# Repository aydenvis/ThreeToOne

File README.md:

# threetoone

*A short description of the keyboard/project*

* Keyboard Maintainer: [Ayden Visser](https://github.com/yourusername)
* Hardware Supported: *The PCBs, controllers supported*
* Hardware Availability: *Links to where you can find this hardware*

Make example for this keyboard (after setting up your build environment):

    make threetoone:default

Flashing example for this keyboard:

    make threetoone:default:flash

See the [build environment setup](https://docs.qmk.fm/#/getting_started_build_tools) and the [make instructions](https://docs.qmk.fm/#/getting_started_make_guide) for more information. Brand new to QMK? Start with our [Complete Newbs Guide](https://docs.qmk.fm/#/newbs).

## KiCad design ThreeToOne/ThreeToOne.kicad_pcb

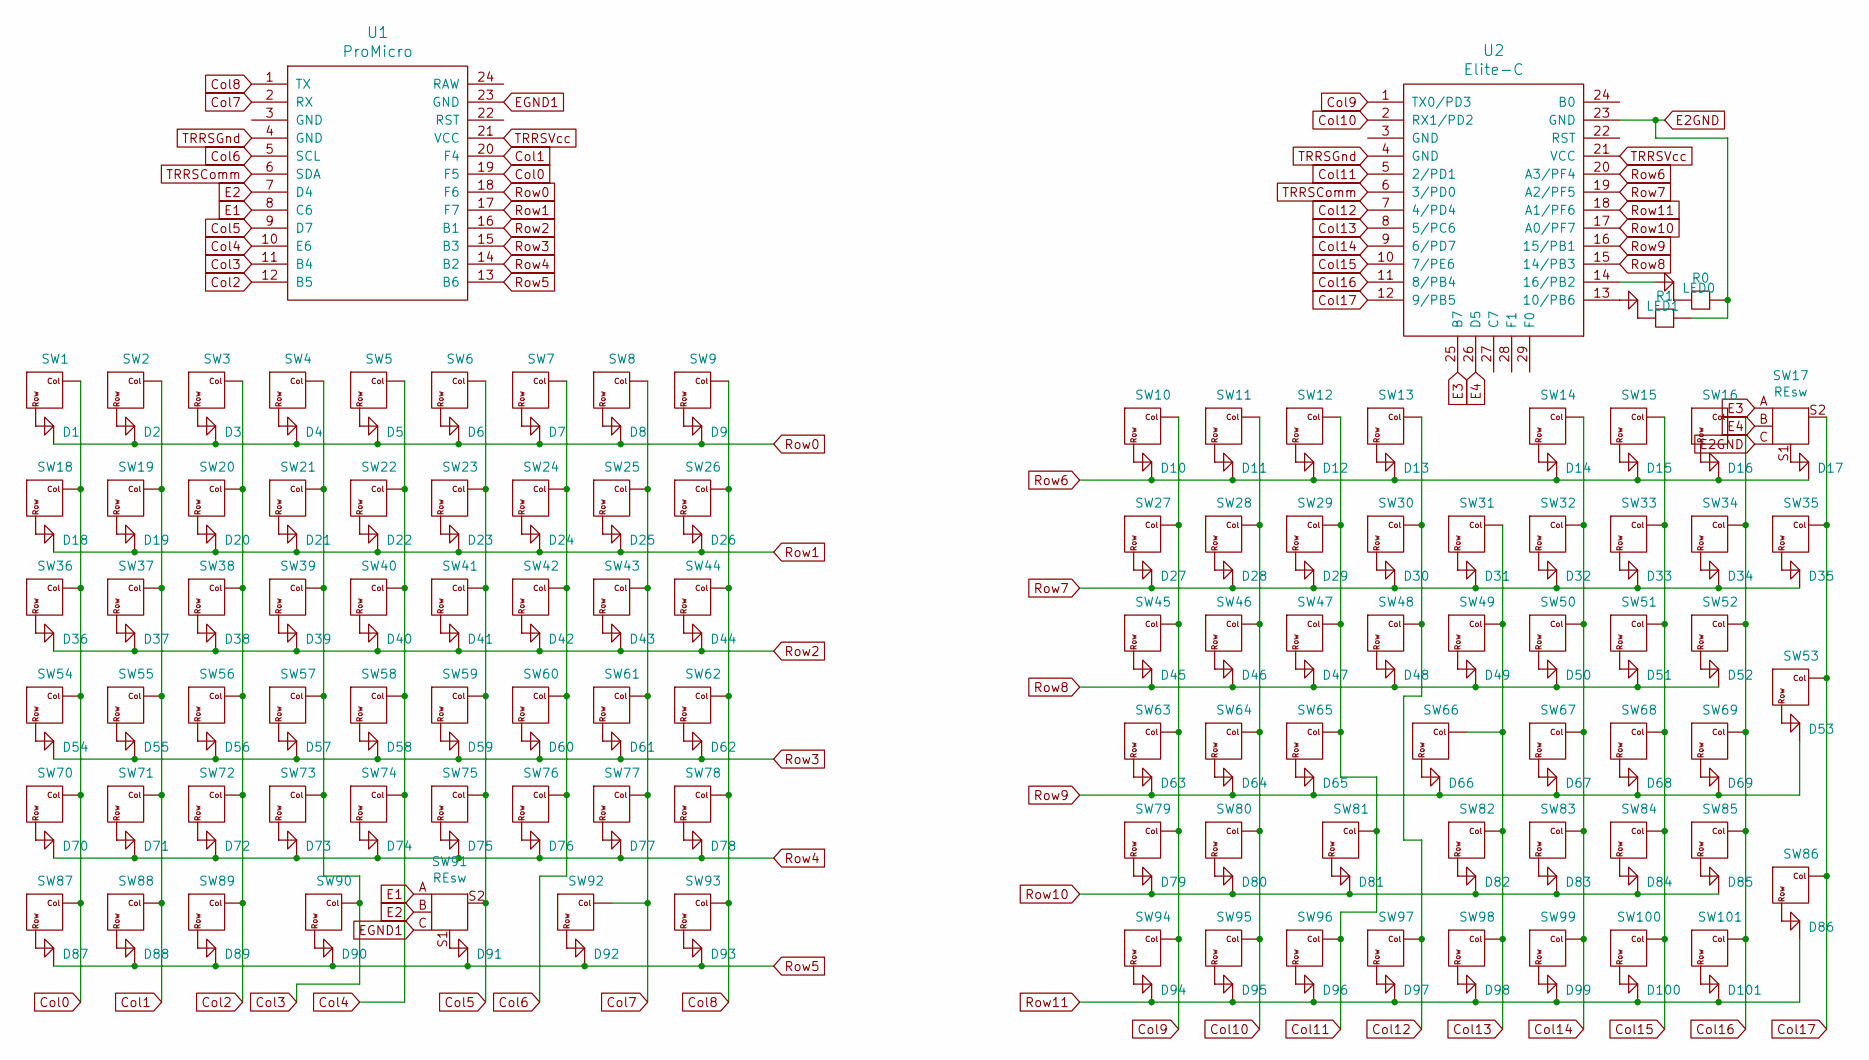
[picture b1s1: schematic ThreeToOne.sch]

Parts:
D1, D2, D3, D4, D5, D6, D7, D8, D9, D10, D11, D12, D13, D14, D15, D16, D17, D18, D19, D20, D21, D22, D23, D24, D25, D26, D27, D28, D29, D30, D31, D32, D33, D34, D35, D36, D37, D38, D39, D40, D41, D42, D43, D44, D45, D46, D47, D48, D49, D50, D51, D52, D53, D54, D55, D56, D57, D58, D59, D60, D61, D62, D63, D64, D65, D66, D67, D68, D69, D70, D71, D72, D73, D74, D75, D76, D77, D78, D79, D80, D81, D82, D83, D84, D85, D86, D87, D88, D89, D90, D91, D92, D93, D94, D95, D96, D97, D98, D99, D100, D101: Diode
LED0, LED1: Diode
R0, R1: Resistor
SW1, SW2, SW3, SW4, SW5, SW6, SW7, SW8, SW9, SW10, SW11, SW12, SW13, SW14, SW15, SW16, SW18, SW19, SW20, SW21, SW22, SW23, SW24, SW25, SW26, SW27, SW28, SW29, SW30, SW31, SW32, SW33, SW34, SW35, SW36, SW37, SW38, SW39, SW40, SW41, SW42, SW43, SW44, SW45, SW46, SW47, SW48, SW49, SW50, SW51, SW52, SW53, SW54, SW55, SW56, SW57, SW58, SW59, SW60, SW61, SW62, SW63, SW64, SW65, SW66, SW67, SW68, SW69, SW70, SW71, SW72, SW73, SW74, SW75, SW76, SW77, SW78, SW79, SW80, SW81, SW82, SW83, SW84, SW85, SW86, SW87, SW88, SW89, SW90, SW92, SW93, SW94, SW95, SW96, SW97, SW98, SW99, SW100, SW101: Switch; MX_Choc_Symmetric
SW17, SW91: REsw
U1: ProMicro
U2: Elite-C

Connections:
Col0: SW1.1, SW18.1, SW36.1, SW54.1, SW70.1, SW87.1, U1.19 (F5)
Col1: SW2.1, SW19.1, SW37.1, SW55.1, SW71.1, SW88.1, U1.20 (F4)
Col2: SW3.1, SW20.1, SW38.1, SW56.1, SW72.1, SW89.1, U1.12 (B5)
Col3: SW4.1, SW21.1, SW39.1, SW57.1, SW73.1, SW90.1, U1.11 (B4)
Col4: SW5.1, SW22.1, SW40.1, SW58.1, SW74.1, U1.10 (E6)
Col5: SW6.1, SW23.1, SW41.1, SW59.1, SW75.1, SW91.S2, U1.9 (D7)
Col6: SW7.1, SW24.1, SW42.1, SW60.1, SW76.1, U1.5 (SCL)
Col7: SW8.1, SW25.1, SW43.1, SW61.1, SW77.1, SW92.1, U1.2 (RX)
Col8: SW9.1, SW26.1, SW44.1, SW62.1, SW78.1, SW93.1, U1.1 (TX)
Col9: SW10.1, SW27.1, SW45.1, SW63.1, SW79.1, SW94.1, U2.1 (TX0/PD3)
Col10: SW11.1, SW28.1, SW46.1, SW64.1, SW80.1, SW95.1, U2.2 (RX1/PD2)
Col11: SW12.1, SW29.1, SW47.1, SW65.1, SW81.1, SW96.1, U2.5 (2/PD1)
Col12: SW13.1, SW30.1, SW48.1, SW97.1, U2.7 (4/PD4)
Col13: SW31.1, SW49.1, SW66.1, SW82.1, SW98.1, U2.8 (5/PC6)
Col14: SW14.1, SW32.1, SW50.1, SW67.1, SW83.1, SW99.1, U2.9 (6/PD7)
Col15: SW15.1, SW33.1, SW51.1, SW68.1, SW84.1, SW100.1, U2.10 (7/PE6)
Col16: SW16.1, SW34.1, SW52.1, SW69.1, SW85.1, SW101.1, U2.11 (8/PB4)
Col17: SW17.S2, SW35.1, SW53.1, SW86.1, U2.12 (9/PB5)
E1: SW91.A, U1.8 (C6)
E2: SW91.B, U1.7 (D4)
E2GND: R0.1, R1.1, SW17.C, U2.23 (GND)
E3: SW17.A, U2.25 (B7)
E4: SW17.B, U2.26 (D5)
EGND1: SW91.C, U1.23 (GND)
unnamed: D1.1 (K), SW1.2
unnamed: D2.1 (K), SW2.2
unnamed: D3.1 (K), SW3.2
unnamed: D4.1 (K), SW4.2
unnamed: D5.1 (K), SW5.2
unnamed: D6.1 (K), SW6.2
unnamed: D7.1 (K), SW7.2
unnamed: D8.1 (K), SW8.2
unnamed: D9.1 (K), SW9.2
unnamed: D10.1 (K), SW10.2
unnamed: D11.1 (K), SW11.2
unnamed: D12.1 (K), SW12.2
unnamed: D13.1 (K), SW13.2
unnamed: D14.1 (K), SW14.2
unnamed: D15.1 (K), SW15.2
unnamed: D16.1 (K), SW16.2
unnamed: D17.1 (K), SW17.S1
unnamed: D18.1 (K), SW18.2
unnamed: D19.1 (K), SW19.2
unnamed: D20.1 (K), SW20.2
unnamed: D21.1 (K), SW21.2
unnamed: D22.1 (K), SW22.2
unnamed: D23.1 (K), SW23.2
unnamed: D24.1 (K), SW24.2
unnamed: D25.1 (K), SW25.2
unnamed: D26.1 (K), SW26.2
unnamed: D27.1 (K), SW27.2
unnamed: D28.1 (K), SW28.2
unnamed: D29.1 (K), SW29.2
unnamed: D30.1 (K), SW30.2
unnamed: D31.1 (K), SW31.2
unnamed: D32.1 (K), SW32.2
unnamed: D33.1 (K), SW33.2
unnamed: D34.1 (K), SW34.2
unnamed: D35.1 (K), SW35.2
unnamed: D36.1 (K), SW36.2
unnamed: D37.1 (K), SW37.2
unnamed: D38.1 (K), SW38.2
unnamed: D39.1 (K), SW39.2
unnamed: D40.1 (K), SW40.2
unnamed: D41.1 (K), SW41.2
unnamed: D42.1 (K), SW42.2
unnamed: D43.1 (K), SW43.2
unnamed: D44.1 (K), SW44.2
unnamed: D45.1 (K), SW45.2
unnamed: D46.1 (K), SW46.2
unnamed: D47.1 (K), SW47.2
unnamed: D48.1 (K), SW48.2
unnamed: D49.1 (K), SW49.2
unnamed: D50.1 (K), SW50.2
unnamed: D51.1 (K), SW51.2
unnamed: D52.1 (K), SW52.2
unnamed: D53.1 (K), SW53.2
unnamed: D54.1 (K), SW54.2
unnamed: D55.1 (K), SW55.2
unnamed: D56.1 (K), SW56.2
unnamed: D57.1 (K), SW57.2
unnamed: D58.1 (K), SW58.2
unnamed: D59.1 (K), SW59.2
unnamed: D60.1 (K), SW60.2
unnamed: D61.1 (K), SW61.2
unnamed: D62.1 (K), SW62.2
unnamed: D63.1 (K), SW63.2
unnamed: D64.1 (K), SW64.2
unnamed: D65.1 (K), SW65.2
unnamed: D66.1 (K), SW66.2
unnamed: D67.1 (K), SW67.2
unnamed: D68.1 (K), SW68.2
unnamed: D69.1 (K), SW69.2
unnamed: D70.1 (K), SW70.2
unnamed: D71.1 (K), SW71.2
unnamed: D72.1 (K), SW72.2
unnamed: D73.1 (K), SW73.2
unnamed: D74.1 (K), SW74.2
unnamed: D75.1 (K), SW75.2
unnamed: D76.1 (K), SW76.2
unnamed: D77.1 (K), SW77.2
unnamed: D78.1 (K), SW78.2
unnamed: D79.1 (K), SW79.2
unnamed: D80.1 (K), SW80.2
unnamed: D81.1 (K), SW81.2
unnamed: D82.1 (K), SW82.2
unnamed: D83.1 (K), SW83.2
unnamed: D84.1 (K), SW84.2
unnamed: D85.1 (K), SW85.2
unnamed: D86.1 (K), SW86.2
unnamed: D87.1 (K), SW87.2
unnamed: D88.1 (K), SW88.2
unnamed: D89.1 (K), SW89.2
unnamed: D90.1 (K), SW90.2
unnamed: D91.1 (K), SW91.S1
unnamed: D92.1 (K), SW92.2
unnamed: D93.1 (K), SW93.2
unnamed: D94.1 (K), SW94.2
unnamed: D95.1 (K), SW95.2
unnamed: D96.1 (K), SW96.2
unnamed: D97.1 (K), SW97.2
unnamed: D98.1 (K), SW98.2
unnamed: D99.1 (K), SW99.2
unnamed: D100.1 (K), SW100.2
unnamed: D101.1 (K), SW101.2
unnamed: LED0.1 (K), U2.14 (16/PB2)
unnamed: LED0.2 (A), R0.2
unnamed: LED1.1 (K), U2.13 (10/PB6)
unnamed: LED1.2 (A), R1.2
Row0: D1.2 (A), D2.2 (A), D3.2 (A), D4.2 (A), D5.2 (A), D6.2 (A), D7.2 (A), D8.2 (A), D9.2 (A), U1.18 (F6)
Row1: D18.2 (A), D19.2 (A), D20.2 (A), D21.2 (A), D22.2 (A), D23.2 (A), D24.2 (A), D25.2 (A), D26.2 (A), U1.17 (F7)
Row2: D36.2 (A), D37.2 (A), D38.2 (A), D39.2 (A), D40.2 (A), D41.2 (A), D42.2 (A), D43.2 (A), D44.2 (A), U1.16 (B1)
Row3: D54.2 (A), D55.2 (A), D56.2 (A), D57.2 (A), D58.2 (A), D59.2 (A), D60.2 (A), D61.2 (A), D62.2 (A), U1.15 (B3)
Row4: D70.2 (A), D71.2 (A), D72.2 (A), D73.2 (A), D74.2 (A), D75.2 (A), D76.2 (A), D77.2 (A), D78.2 (A), U1.14 (B2)
Row5: D87.2 (A), D88.2 (A), D89.2 (A), D90.2 (A), D91.2 (A), D92.2 (A), D93.2 (A), U1.13 (B6)
Row6: D10.2 (A), D11.2 (A), D12.2 (A), D13.2 (A), D14.2 (A), D15.2 (A), D16.2 (A), D17.2 (A), U2.20 (A3/PF4)
Row7: D27.2 (A), D28.2 (A), D29.2 (A), D30.2 (A), D31.2 (A), D32.2 (A), D33.2 (A), D34.2 (A), D35.2 (A), U2.19 (A2/PF5)
Row8: D45.2 (A), D46.2 (A), D47.2 (A), D48.2 (A), D49.2 (A), D50.2 (A), D51.2 (A), D52.2 (A), U2.15 (14/PB3)
Row9: D53.2 (A), D63.2 (A), D64.2 (A), D65.2 (A), D66.2 (A), D67.2 (A), D68.2 (A), D69.2 (A), U2.16 (15/PB1)
Row10: D79.2 (A), D80.2 (A), D81.2 (A), D82.2 (A), D83.2 (A), D84.2 (A), D85.2 (A), U2.17 (A0/PF7)
Row11: D86.2 (A), D94.2 (A), D95.2 (A), D96.2 (A), D97.2 (A), D98.2 (A), D99.2 (A), D100.2 (A), D101.2 (A), U2.18 (A1/PF6)
TRRSComm: U1.6 (SDA), U2.6 (3/PD0)
TRRSGnd: U1.4 (GND), U2.4 (GND)
TRRSVcc: U1.21 (VCC), U2.21 (VCC)

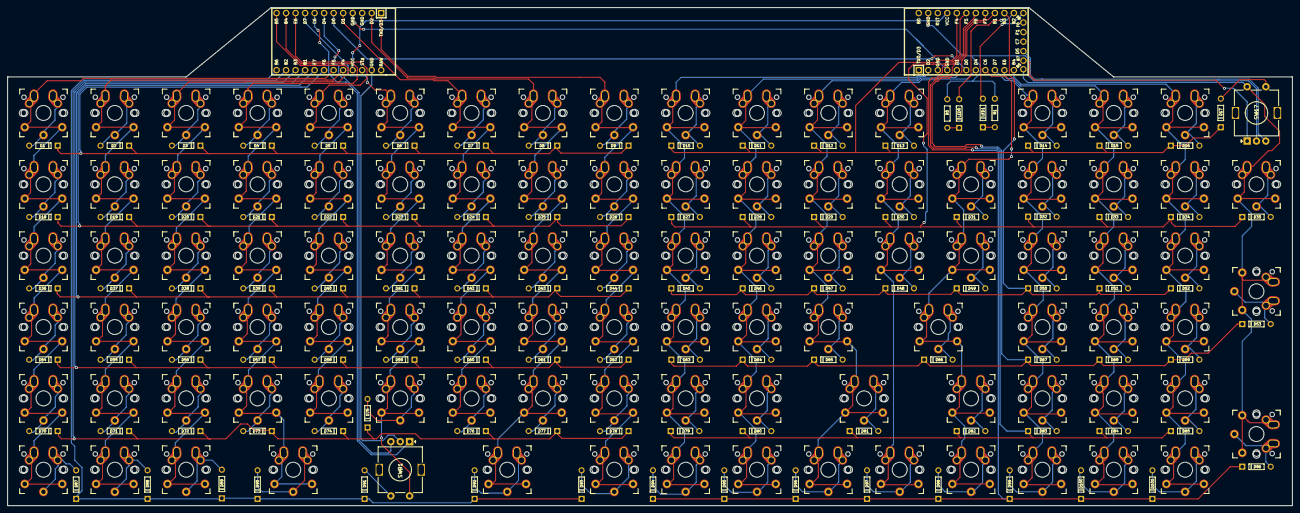
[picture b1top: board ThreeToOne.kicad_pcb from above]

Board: 2 copper layers, 343.0 x 133.0 mm, 208 parts (0 on the bottom side), 144 nets.

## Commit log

2021-03-13 First layout
2021-03-13 Assigned footprints
2021-03-13 Footprints laid out
2021-03-13 Laid out and routed rows/cols
2021-03-17 Wired all of left half and some of right
2021-03-17 Finished + gerbers
2021-03-19 moved enc to the left
2021-03-28 Finalization
2021-04-05 Added QMK folder
2021-05-04 final edit
2021-07-05 Updated to QMK Ver 13.17 and added default hexfile
2021-07-06 fixed space issue
2021-08-05 updated scroll direction
